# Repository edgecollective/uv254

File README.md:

# uv254

**[⬇ Download the latest files (zip)](https://github.com/edgecollective/uv254/archive/refs/heads/main.zip)**:
everything on `main` (all three KiCad boards, the shared parts library and the
firmware), as of the [latest commit](https://github.com/edgecollective/uv254/commit/main).
Unzip it and keep the folders together.

**Release v0.6** (2026-11-23), the three boards as one set that work together:
gerbers for the [detector](https://github.com/edgecollective/uv254/releases/download/uv-detector/v0.6/uv-detector-v0.6-gerbers.zip),
[emitter](https://github.com/edgecollective/uv254/releases/download/uv-emitter/v0.6/uv-emitter-v0.6-gerbers.zip) and
[control](https://github.com/edgecollective/uv254/releases/download/uv-control/v0.6/uv-control-v0.6-gerbers.zip) boards
(release pages: [detector](https://github.com/edgecollective/uv254/releases/tag/uv-detector/v0.6),
[emitter](https://github.com/edgecollective/uv254/releases/tag/uv-emitter/v0.6),
[control](https://github.com/edgecollective/uv254/releases/tag/uv-control/v0.6)), or
**[⬇ the whole design at this release (zip)](https://github.com/edgecollective/uv254/archive/refs/tags/uv-control/v0.6.zip)**.
Unlike the "latest" link above, these stay the same when more commits are pushed.

Open hardware for the **uv254** UV water-quality sensor. The device is three
boards, each its own KiCad project:

| Board | Folder | What's on it | Current design |
|---|---|---|---|
| **UV-Control** | [`hardware/uv-control`](hardware/uv-control) | Adafruit Feather controller (nRF52840 or ESP32-S3), ADS1115 ADC, color TFT, microSD, buttons, 12 V LED boost | v0.6 (released 2026-11-23) |
| **UV-Emitter** | [`hardware/uv-emitter`](hardware/uv-emitter) | Inolux IN-C35PPCTGU0 UV-C LED and its driver | v0.6 (released 2026-11-23: 3.3 V, 12 V LED supply, MMBT3904 driver) |
| **UV-Detector** | [`hardware/uv-detector`](hardware/uv-detector) | SD008-2171-112 photodiode with an op-amp front end | v0.6 (released 2026-11-23: 3.3 V, 1.8 V reference, 7-pin connector) |

| [UV-Control](hardware/uv-control) | [UV-Emitter](hardware/uv-emitter) | [UV-Detector](hardware/uv-detector) |
|:---:|:---:|:---:|
|  |  |  |

Each board's README has its schematic, PCB layout and 3D views.

**Open work:** [`hardware/uv-control/TODO.md`](hardware/uv-control/TODO.md) is
the to-do list for the control board (v0.4 layout in progress). If you're a
person or an agent picking up the work, read it and
[CONTRIBUTING.md](CONTRIBUTING.md) first.

**Bill of materials:** [`hardware/BOM.md`](hardware/BOM.md) lists the parts for
one set of boards and the cables between them, with manufacturer part numbers.
The same list is on the [project web page](https://edgecollective.io/uv254/bom/),
which scales it to several sets and downloads it as a CSV for Digi-Key's or
Mouser's BOM upload.

UV-Emitter was called *UV-LED-source* in earlier revisions. Background notes
are at <https://edgecollective.io/notes/uvf/>.

## Repository layout

```
hardware/
  BOM.md, bom.csv             parts for one set of boards and cables, with part numbers
  uv-control/                 one KiCad project per board
    uv-control.kicad_pro      open this in KiCad
    uv-control.kicad_sch
    uv-control.kicad_pcb
    TODO.md                   open work on that board (uv-control has one)
    sym-lib-table             -> lib/uv254.kicad_sym
    fp-lib-table              -> lib/uv254.pretty
    docs/                     schematic PDF and the images in the board's README
    fab/<version>/            fabrication files that were actually sent out
  uv-emitter/
  uv-detector/
lib/                          shared project library (custom parts only)
  uv254.kicad_sym
  uv254.pretty/
firmware/uv-control/          CircuitPython scripts for the control board
docs/                         project web page (GitHub Pages): edgecollective.io/uv254
  bom/index.html              the bill of materials page, made by scripts/make-bom.py
scripts/build-fab.sh          builds gerbers, drill, BOM, PDF, positions
scripts/render-images.sh      renders schematic, layout and 3D images for the READMEs
scripts/make-bom.py           builds BOM.md, bom.csv and the BOM web page from the schematics
.github/workflows/kicad.yml   ERC/DRC on every push; fab package on release tags
```

## Opening the boards

**[Download the latest design files (zip)](https://github.com/edgecollective/uv254/archive/refs/heads/main.zip)** if you just want to look
at or build the boards, or clone the repository to work on them. Either way,
open `hardware/<board>/<board>.kicad_pro` in **KiCad 10.0.x**, the version
everyone on the project uses (see [CONTRIBUTING.md](CONTRIBUTING.md)).

Keep the folder structure as it is. Custom parts come from `lib/` through each
project's own library tables, so you don't need any global library setup beyond
KiCad's standard libraries, but a board folder copied out on its own will be
missing its custom parts.

## Updating the board images

Each board's README shows its schematic, PCB layout and 3D views. These are
files in `hardware/<board>/docs/`, made by `scripts/render-images.sh`, so they
don't change by themselves when the design does. After changing a board, save
it in KiCad, then refresh the images from the top of the repository:

```sh
scripts/render-images.sh uv-detector                         # one board
scripts/render-images.sh uv-control uv-detector uv-emitter   # all three
```

Then commit what changed (`git status` shows it) along with the design change.

What the script does:

- Writes to `hardware/<board>/docs/`: the schematic as PDF and PNG, the PCB
  layout front and back (the back mirrored, as seen from below), and 3D renders
  front and back.
- Updates the image section of the board's README, between the
  `render-images` markers. Anything you write between those markers gets
  overwritten, so put your own notes outside them.
- Only replaces files whose picture changed. A board whose 3D look changed
  takes about 2 minutes (two raytraced renders). An unchanged board takes about
  15 seconds and leaves git clean.
- Uses KiCad's default colour theme, so everyone's images come out the same
  whatever their own KiCad preferences.

For a quick look while you work, `--fast` makes flat-shaded 3D renders in a few
seconds. Commit the full renders, though: run it again without `--fast` before
committing.

It needs KiCad 10 (`kicad-cli` on your `PATH`), plus Inkscape, ImageMagick and
poppler. On Debian or Ubuntu:

```sh
sudo apt install inkscape imagemagick poppler-utils
```

It has only been tested on Linux.

## Updating the bill of materials

`hardware/BOM.md`, `hardware/bom.csv` and the web page `docs/bom/index.html`
are made by `scripts/make-bom.py` from the three schematics. After adding,
removing or changing parts, run it from the top of the repository and commit
what changed:

```sh
scripts/make-bom.py
```

The schematics don't carry part numbers, so the script keeps its own table of
them (`PARTS`, near the top). If a schematic has a part the script doesn't
know, it stops and names it: add a line for it to `PARTS` and to `part_for()`.
Files only change when the parts do, so re-running leaves git clean otherwise.
It needs `kicad-cli` on your `PATH`.

The web page is served by GitHub Pages from the `docs/` folder on `main`, at
<https://edgecollective.io/uv254/>, the address printed on the detector and
emitter boards. It updates a minute or so after a push.

## Versions and releases

Each board is versioned on its own. A revision is a git tag named
`<board>/<version>`:

```
git tag -l 'uv-detector/*'          # list detector revisions
git checkout uv-detector/v0.3       # the exact design ordered from JLCPCB in Aug 2024
git checkout main                   # back to the current work
```

To download one revision as a zip, use its tag, for example
<https://github.com/edgecollective/uv254/archive/refs/tags/uv-detector/v0.3.zip>.

`hardware/<board>/fab/<version>/` holds the files that were actually sent to
the fab house for that revision. Each board's README has the revision history.
Pushing a new tag makes CI build that board's fab package and attach it to a
GitHub Release (see [CONTRIBUTING.md](CONTRIBUTING.md#releasing-a-board-revision)).

The history before this repository is in
[gitlab.com/edgecollective/uv-water](https://gitlab.com/edgecollective/uv-water).
Every tagged revision here was imported from it. The imported fab files were
checked by regenerating them from the tagged design.

## License

- **Hardware** (everything except `firmware/`): [CERN Open Hardware Licence
  Version 2 – Strongly Reciprocal](LICENSE) (CERN-OHL-S-2.0).
- **Exception:** `lib/uv254.3dshapes/Adafruit_Feather_nRF52840_4062.step` and
  `Adafruit_TPS61040_Boost_5644.step` are Adafruit's 3D models, under the MIT
  License ([notice](lib/uv254.3dshapes/Adafruit_CAD_Parts-LICENSE.txt)).
- **Firmware** (`firmware/`): [MIT License](firmware/uv-control/LICENSE). The
  bundled Adafruit libraries are also MIT, under Adafruit's copyright.

Contributors: Don Blair, Craig Versek.

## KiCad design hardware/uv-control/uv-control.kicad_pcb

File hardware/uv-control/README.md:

# UV-Control

Controller board. **v0.6 was released on 2026-11-23** (tag `uv-control/v0.6`,
fab files in [`fab/v0.6`](fab/v0.6)), with the detector and emitter v0.6 it connects to. It was restarted from Rook v0.4 (Edge
Collective's validated Pro Micro nRF52840 board) and keeps its ST7789 display,
buttons and microSD, with an **Adafruit Feather** (nRF52840 or ESP32-S3, M4 as
fallback) as the controller, an ADS1115 ADC, JST connectors to the emitter and
detector, test headers, a power switch, and a TPS61041 boost that makes the UV
LED's 12 V (or Adafruit's 5644 boost breakout at J8). Firmware is moving to Arduino.
See [`v0.4-design.md`](v0.4-design.md) for the pin map. The
first v0.4 draft is in [`reference/v0.4-draft`](reference/v0.4-draft).

**Open work: [`TODO.md`](TODO.md)** lists what's left before ordering, with
part references, coordinates and how to check each item. Start there if you're
picking up this board (people and agents alike).

v0.1 (fabricated in 2024) used an Adafruit ItsyBitsy nRF52840 Express, an
SSD1306 OLED display, push buttons and a 555-based boost circuit.

Firmware is in [`firmware/uv-control`](../../firmware/uv-control). The v0.4
bring-up code is in its [`v0.4`](../../firmware/uv-control/v0.4) folder.

Open `uv-control.kicad_pro` in KiCad 10. Custom parts come from
[`lib/`](../../lib).

**[Download the KiCad files (zip)](https://github.com/edgecollective/uv254/archive/refs/heads/main.zip)**: the whole repository as it is on
`main`, because the board needs the shared `lib/` folder. This board is in
`hardware/uv-control/`.

<!-- render-images:start -->
<!-- Generated by scripts/render-images.sh. Edits between these markers are overwritten. -->

## Schematic

Click the image for the [PDF](docs/uv-control-schematic.pdf).

## Board layout

Copper and silkscreen. The back is mirrored, as seen from below.

| Front | Back |
|:---:|:---:|
|  |  |

## 3D view

| Front | Back |
|:---:|:---:|
|  |  |

Images of the current design, made with `scripts/render-images.sh uv-control`.
Re-run it after changing the board; see
[Updating the board images](../../README.md#updating-the-board-images).
<!-- render-images:end -->

## Revisions

| Version | Date | Status | Design | Fab files |
|---|---|---|---|---|
| v0.1 | 2024-07-29 | gerbers released; ordered from JLCPCB on 2024-08-19 | tag `uv-control/v0.1` | [`fab/v0.1`](fab/v0.1) |
| v0.1_A | 2026-06-26 | branched from v0.1; sent to Josh | tag `uv-control/v0.1_A` | — |
| v0.1_A+ | 2026-10 | edits made after v0.1_A was sent; never fabricated; superseded by v0.4 | commit `db4232b` | — |
| v0.4 | 2026-11-23 | tagged, then renumbered v0.5 before ordering (same design) | tag `uv-control/v0.4` | [`fab/v0.4`](fab/v0.4) |
| v0.5 | 2026-11-23 | released, then superseded by v0.6 before ordering | tag `uv-control/v0.5` | [`fab/v0.5`](fab/v0.5) |
| **v0.6** | 2026-11-23 | **released**: v0.5 plus pin labels at the display header; for detector and emitter v0.6 (open items in [`TODO.md`](TODO.md)) | tag `uv-control/v0.6` | [`fab/v0.6`](fab/v0.6) |

Notes:

- **v0.1_A+** isn't tagged. To get it back: `git checkout db4232b -- hardware/uv-control`.
  Its silkscreen points to `gitlab.com/edgecollective/uv-water/` and reads
  `UV-Control v0.1 / July 2024`.

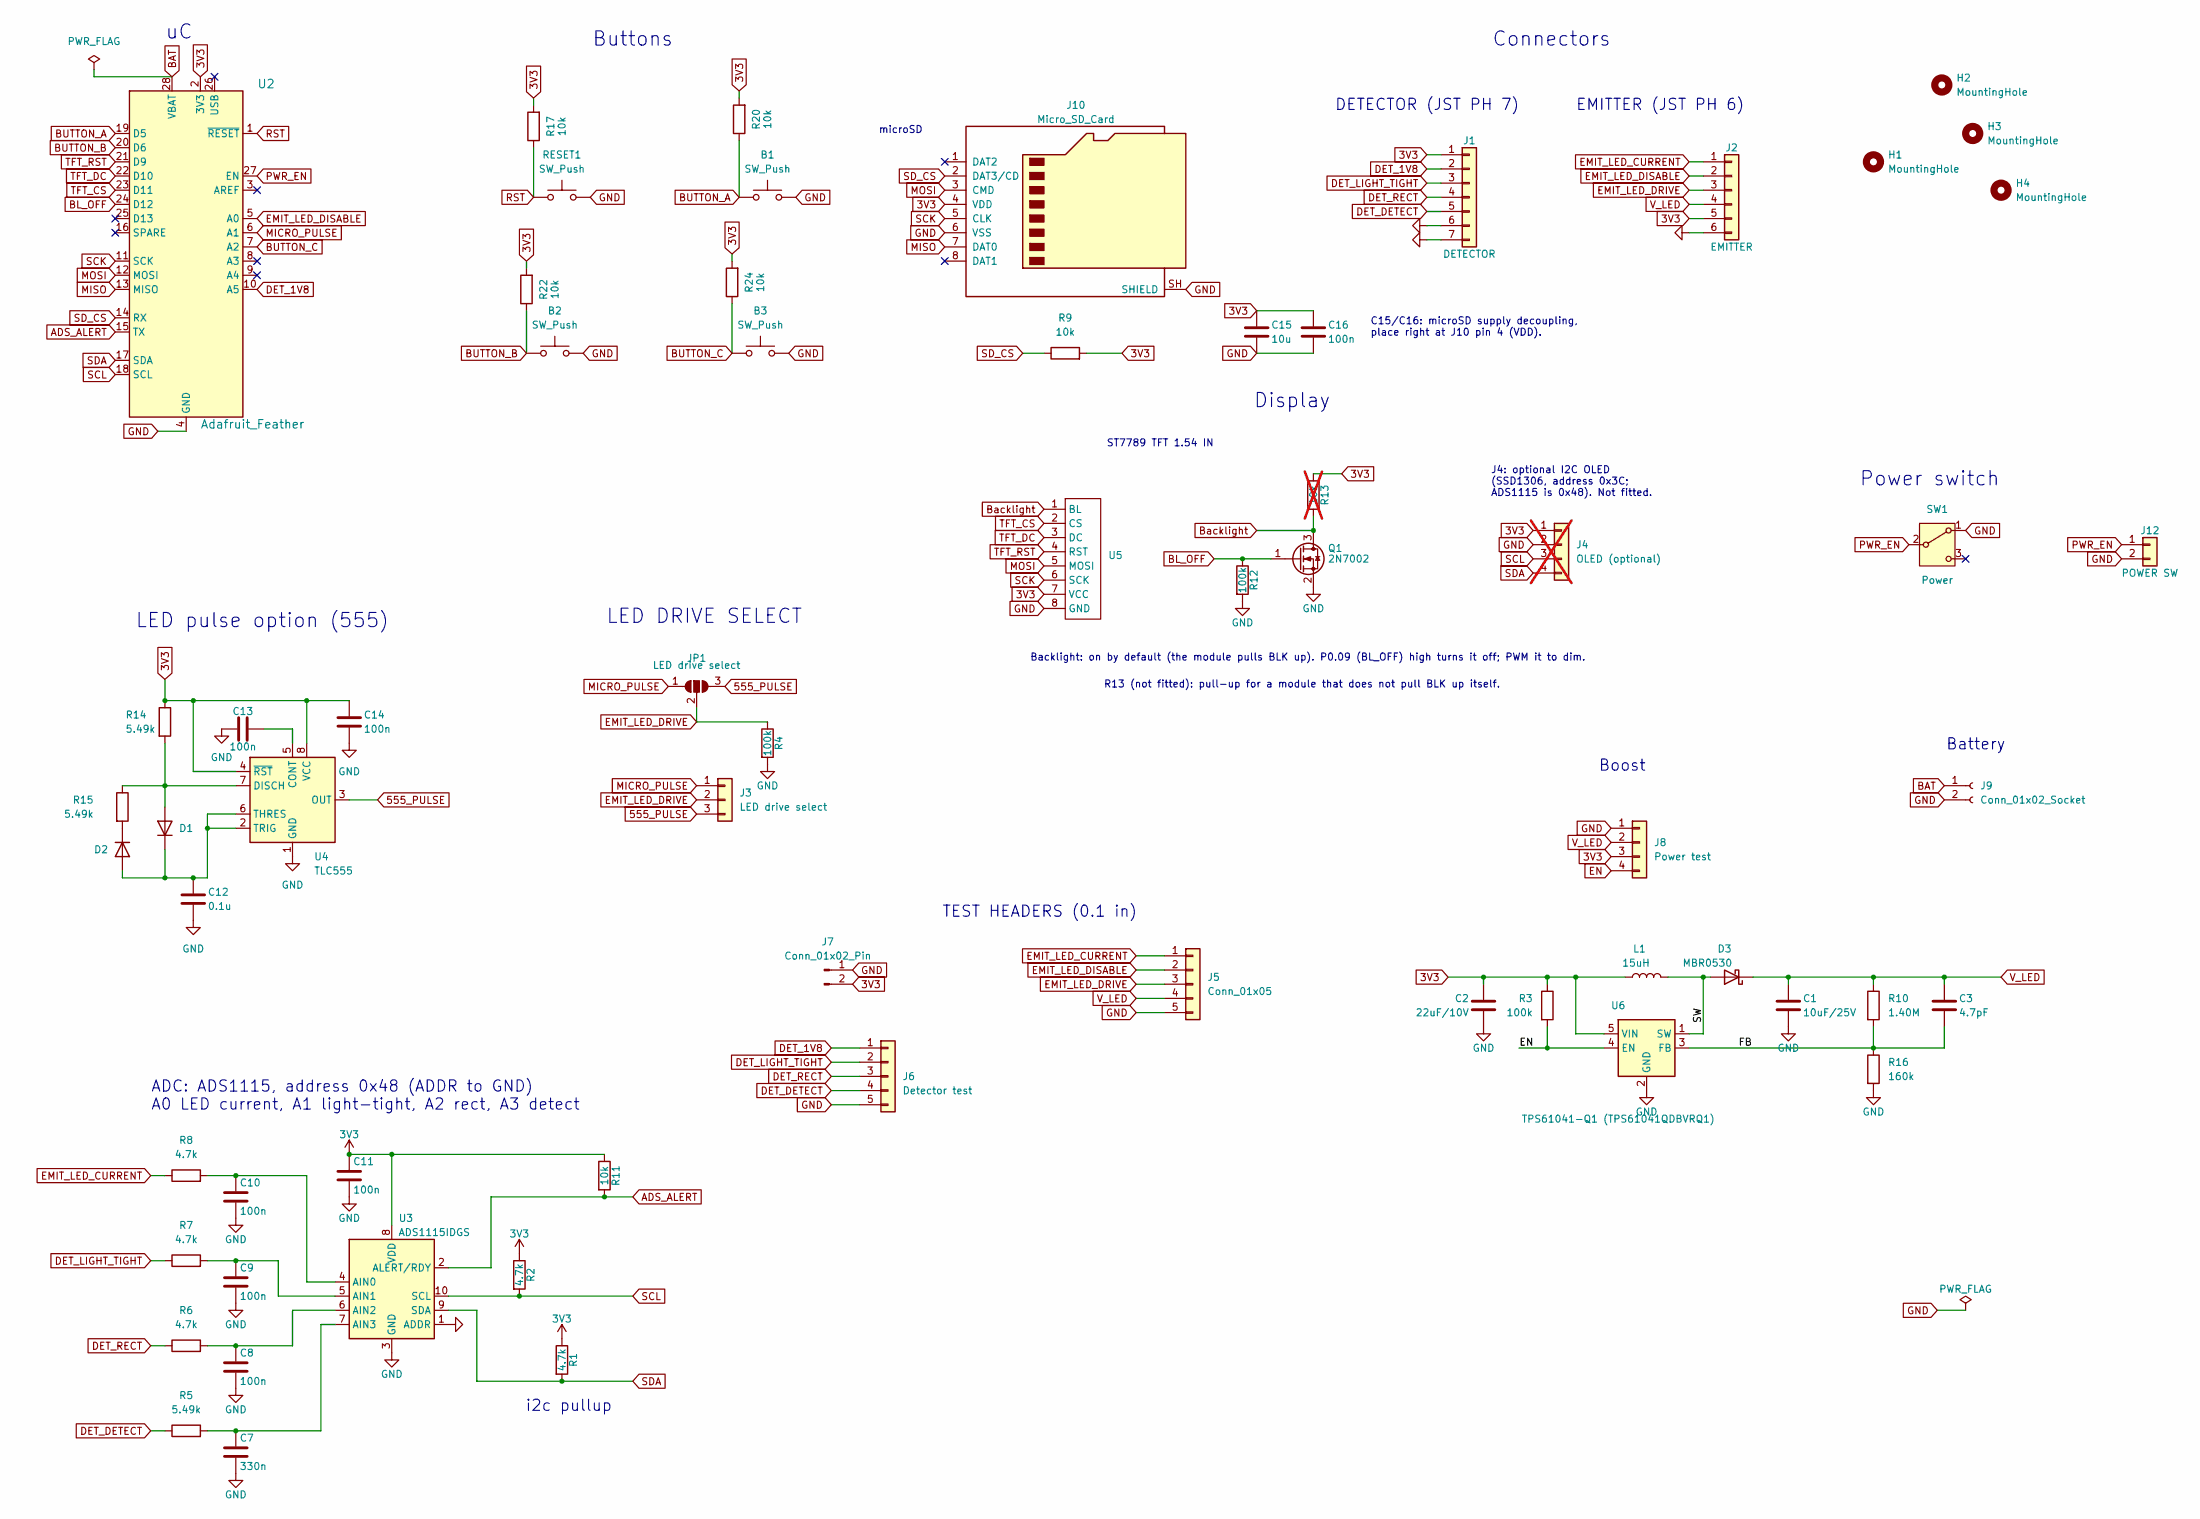
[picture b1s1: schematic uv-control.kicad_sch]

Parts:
B1, B2, B3: SW_Push; SW_Tactile_12x12_B3F-40xx
C1: 10uF/25V; C_0805_2012Metric
C2: 22uF/10V; C_0805_2012Metric
C3: 4.7pF; C_0805_2012Metric
C7: 330n; C_0805_2012Metric
C8, C9, C10, C11, C13, C14, C16: 100n; C_0805_2012Metric
C12: 0.1u; C_0805_2012Metric
C15: 10u; C_0805_2012Metric
D1, D2: 1N4148W; D_SOD-123
D3: MBR0530; D_SOD-123
H1, H2, H3, H4: MountingHole; MountingHole_3.2mm_M3
J1: DETECTOR; JST_PH_B7B-PH-K_1x07_P2.00mm_Vertical
J2: EMITTER; JST_PH_B6B-PH-K_1x06_P2.00mm_Vertical
J3: LED drive select; PinHeader_1x03_P2.54mm_Vertical
J4: OLED (optional); ssd1306_a; not fitted
J5: Conn_01x05; PinHeader_1x05_P2.54mm_Vertical
J6: Detector test; PinHeader_1x05_P2.54mm_Vertical
J7: Conn_01x02_Pin; PinHeader_1x02_P2.54mm_Vertical
J8: Power test; Adafruit_TPS61040_Boost_5644
J9: Conn_01x02_Socket; JST_PH_B2B-PH-K_1x02_P2.00mm_Vertical
J10: Micro_SD_Card; DM3D-SF_outline
J12: POWER SW; PinHeader_1x02_P2.54mm_Vertical
JP1: LED drive select; SolderJumper-3_P1.3mm_Open_RoundedPad1.0x1.5mm_NumberLabels
L1: 15uH; L_1210_3225Metric
Q1: 2N7002; SOT-23
R1, R2, R6, R7, R8: 4.7k; R_0805_2012Metric
R3: 100k; R_0603_1608Metric
R4, R12: 100k; R_0805_2012Metric
R5, R14, R15: 5.49k; R_0805_2012Metric
R9, R17, R20, R22, R24: 10k; R_0805_2012Metric_Pad1.20x1.40mm_HandSolder
R10: 1.40M; R_0805_2012Metric_Pad1.20x1.40mm_HandSolder
R11: 10k; R_0805_2012Metric
R13: 10k; R_0805_2012Metric; not fitted
R16: 160k; R_0805_2012Metric
RESET1: SW_Push; SW_PUSH_6mm_H5mm
SW1: Power; SW_Slide_SPDT_Angled_CK_OS102011MA1Q
U2: Adafruit_Feather; Adafruit_Feather_on_socket_WithMountingHoles
U3: ADS1115IDGS; TSSOP-10_3x3mm_P0.5mm
U4: TLC555; SOIC-8_3.9x4.9mm_P1.27mm
U5: st7789_200in_240x320
U6: TPS61041-Q1 (TPS61041QDBVRQ1); SOT-23-5

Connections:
3V3: C2.1, C11.1, C14.1, C15.1, C16.1, J1.1, J2.5, J4.1, J7.2, J8.3, J10.4 (VDD), L1.1, R1.1, R2.1, R3.1, R9.2, R11.1, R13.1, R14.1, R17.2, R20.2, R22.2, R24.2, U2.2 (3V3), U3.8 (VDD), U4.4 (~RST), U4.8 (VCC), U5.7 (VCC), U6.5 (VIN)
555_PULSE: J3.3, JP1.3 (B), U4.3 (OUT)
/FB: C3.2, R10.2, R16.1, U6.3 (FB)
/SW: D3.2 (A), L1.2, U6.1 (SW)
ADS_ALERT: R11.2, U2.15 (TX), U3.2 (ALERT/RDY)
BAT: J9.1, U2.28 (VBAT)
BL_OFF: Q1.1 (G), R12.1, U2.24 (D12)
BUTTON_A: B1.1, R20.1, U2.19 (D5)
BUTTON_B: B2.1, R22.1, U2.20 (D6)
BUTTON_C: B3.1, R24.1, U2.7 (A2)
Backlight: Q1.3 (D), R13.2, U5.1 (BL)
DET_1V8: J1.2, J6.1, U2.10 (A5)
DET_DETECT: J1.5, J6.4, R5.1
DET_LIGHT_TIGHT: J1.3, J6.2, R7.1
DET_RECT: J1.4, J6.3, R6.1
EMIT_LED_CURRENT: J2.1, J5.1, R8.1
EMIT_LED_DISABLE: J2.2, J5.2, U2.5 (A0)
EMIT_LED_DRIVE: J2.3, J3.2, J5.3, JP1.2 (C), R4.1
EN: J8.4, R3.2, U6.4 (EN)
GND: B1.2, B2.2, B3.2, C1.2, C2.2, C7.2, C8.2, C9.2, C10.2, C11.2, C12.2, C13.1, C14.2, C15.2, C16.2, J1.6, J1.7, J2.6, J4.2, J5.5, J6.5, J7.1, J8.1, J9.2, J10.6 (VSS), J10.SH (SHIELD), J12.2, Q1.2 (S), R4.2, R12.2, R16.2, RESET1.2, SW1.1 (A), U2.4 (GND), U3.1 (ADDR), U3.3 (GND), U4.1 (GND), U5.8 (GND), U6.2 (GND)
MICRO_PULSE: J3.1, JP1.1 (A), U2.6 (A1)
MISO: J10.7 (DAT0), U2.13 (MISO)
MOSI: J10.3 (CMD), U2.12 (MOSI), U5.5 (MOSI)
unnamed: D1.2 (A), R14.2, R15.1, U4.7 (DISCH)
unnamed: C12.1, D1.1 (K), D2.2 (A), U4.2 (TRIG), U4.6 (THRES)
unnamed: D2.1 (K), R15.2
unnamed: C10.1, R8.2, U3.4 (AIN0)
unnamed: C9.1, R7.2, U3.5 (AIN1)
unnamed: C8.1, R6.2, U3.6 (AIN2)
unnamed: C7.1, R5.2, U3.7 (AIN3)
unnamed: C13.2, U4.5 (CONT)
PWR_EN: J12.1, SW1.2 (B), U2.27 (EN)
RST: R17.1, RESET1.1, U2.1 (~RESET)
SCK: J10.5 (CLK), U2.11 (SCK), U5.6 (SCK)
SCL: J4.3, R2.2, U2.18 (SCL), U3.10 (SCL)
SDA: J4.4, R1.2, U2.17 (SDA), U3.9 (SDA)
SD_CS: J10.2 (DAT3/CD), R9.1, U2.14 (RX)
TFT_CS: U2.23 (D11), U5.2 (CS)
TFT_DC: U2.22 (D10), U5.3 (DC)
TFT_RST: U2.21 (D9), U5.4 (RST)
V_LED: C1.1, C3.1, D3.1 (K), J2.4, J5.4, J8.2, R10.1

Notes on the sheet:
LED DRIVE SELECT
Boost
microSD
EMITTER (JST PH 6)
Display
TEST HEADERS (0.1 in)
ADC: ADS1115, address 0x48 (ADDR to GND) A0 LED current, A1 light-tight, A2 rect, A3 detect
ST7789 TFT 1.54 IN
Connectors
Battery
i2c pullup
DETECTOR (JST PH 7)
Power switch
Backlight: on by default (the module pulls BLK up). P0.09 (BL_OFF) high turns it off; PWM it to dim.
C15/C16: microSD supply decoupling, place right at J10 pin 4 (VDD).
Buttons
LED pulse option (555)
R13 (not fitted): pull-up for a module that does not pull BLK up itself.
J4: optional I2C OLED (SSD1306, address 0x3C; ADS1115 is 0x48). Not fitted.

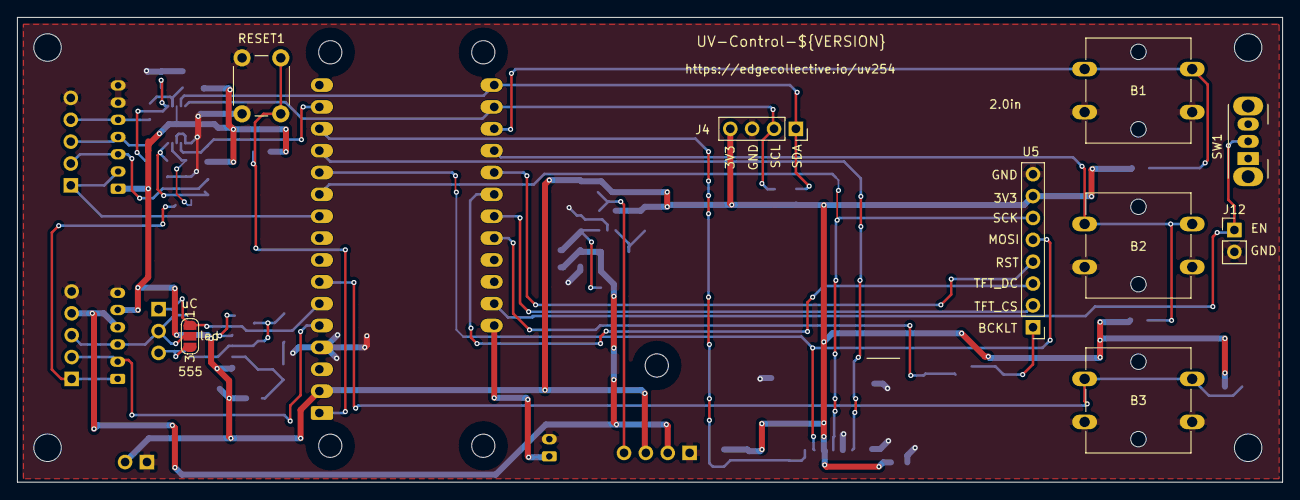
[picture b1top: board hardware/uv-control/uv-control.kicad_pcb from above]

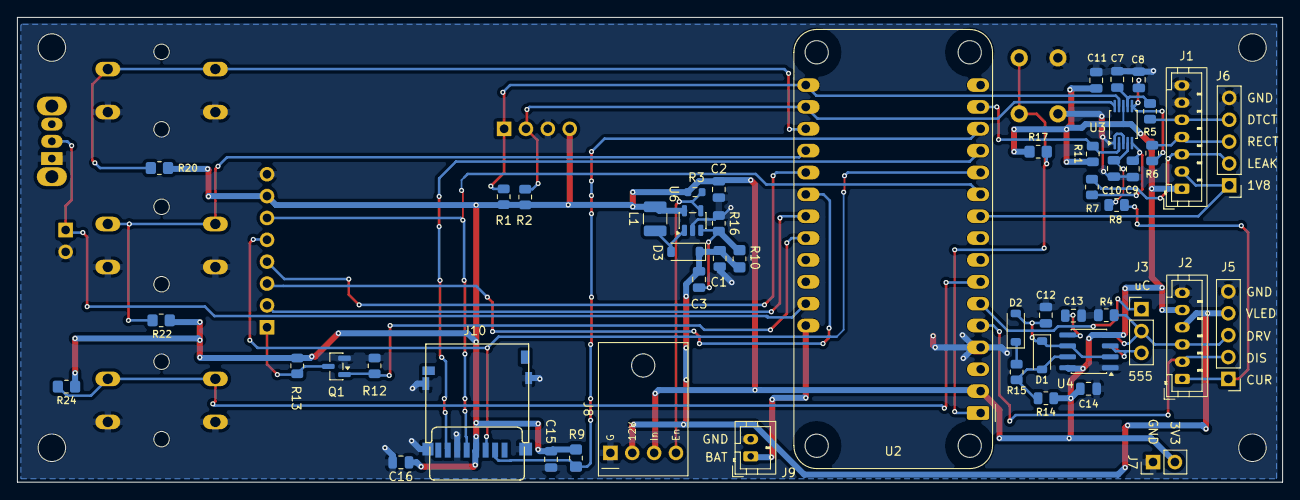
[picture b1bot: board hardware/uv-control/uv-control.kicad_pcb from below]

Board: 2 copper layers, 147.0 x 54.0 mm, 64 parts (51 on the bottom side), 41 nets.

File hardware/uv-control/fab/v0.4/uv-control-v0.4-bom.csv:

"Refs","Value","Footprint","Qty","DNP","Description"
"B1,B2,B3","SW_Push","uv254:SW_Tactile_12x12_B3F-40xx","3","","Push button switch, generic, two pins"
"C1","10uF/25V","Capacitor_SMD:C_0805_2012Metric","1","",""
"C2","22uF/10V","Capacitor_SMD:C_0805_2012Metric","1","",""
"C3","4.7pF","Capacitor_SMD:C_0805_2012Metric","1","",""
"C7","330n","Capacitor_SMD:C_0805_2012Metric","1","","Unpolarized capacitor"
"C8,C9,C10,C11,C13,C14,C16","100n","Capacitor_SMD:C_0805_2012Metric","7","","Unpolarized capacitor"
"C12","0.1u","Capacitor_SMD:C_0805_2012Metric","1","","Unpolarized capacitor"
"C15","10u","Capacitor_SMD:C_0805_2012Metric","1","","Unpolarized capacitor"
"D1,D2","1N4148W","Diode_SMD:D_SOD-123","2","","75V 0.15A Fast Switching Diode, SOD-123"
"D3","MBR0530","Diode_SMD:D_SOD-123","1","",""
"J1","DETECTOR","Connector_JST:JST_PH_B7B-PH-K_1x07_P2.00mm_Vertical","1","","Generic connector, single row, 01x07, script generated (kicad-library-utils/schlib/autogen/connector/)"
"J2","EMITTER","Connector_JST:JST_PH_B6B-PH-K_1x06_P2.00mm_Vertical","1","","Generic connector, single row, 01x06, script generated (kicad-library-utils/schlib/autogen/connector/)"
"J3","LED drive select","Connector_PinHeader_2.54mm:PinHeader_1x03_P2.54mm_Vertical","1","","Generic connector, single row, 01x03, script generated (kicad-library-utils/schlib/autogen/connector/)"
"J4","OLED (optional)","uv254:ssd1306_a","1","DNP","Generic connector, single row, 01x04, script generated (kicad-library-utils/schlib/autogen/connector/)"
"J5","Conn_01x05","Connector_PinHeader_2.54mm:PinHeader_1x05_P2.54mm_Vertical","1","","Generic connector, single row, 01x05, script generated (kicad-library-utils/schlib/autogen/connector/)"
"J6","Detector test","Connector_PinHeader_2.54mm:PinHeader_1x05_P2.54mm_Vertical","1","","Generic connector, single row, 01x05, script generated (kicad-library-utils/schlib/autogen/connector/)"
"J7","Conn_01x02_Pin","Connector_PinHeader_2.54mm:PinHeader_1x02_P2.54mm_Vertical","1","","Generic connector, single row, 01x02, script generated"
"J8","Power test","uv254:Adafruit_TPS61040_Boost_5644","1","","Generic connector, single row, 01x04, script generated (kicad-library-utils/schlib/autogen/connector/)"
"J9","Conn_01x02_Socket","Connector_JST:JST_PH_B2B-PH-K_1x02_P2.00mm_Vertical","1","","Generic connector, single row, 01x02, script generated"
"J10","Micro_SD_Card","uv254:DM3D-SF_outline","1","","Micro SD Card Socket"
"J12","POWER SW","Connector_PinHeader_2.54mm:PinHeader_1x02_P2.54mm_Vertical","1","","Panel-mount power switch (e.g. a rocker), in parallel with SW1: closed pulls the Feather EN pin to GND (off)"
"L1","15uH","Inductor_SMD:L_1210_3225Metric","1","",""
"Q1","2N7002","Package_TO_SOT_SMD:SOT-23","1","","0.115A Id, 60V Vds, N-Channel MOSFET, SOT-23"
"R1,R2,R6,R7,R8","4.7k","Resistor_SMD:R_0805_2012Metric","5","","Resistor"
"R3","100k","Resistor_SMD:R_0603_1608Metric","1","",""
"R4,R12","100k","Resistor_SMD:R_0805_2012Metric","2","","Resistor"
"R5,R14,R15","5.49k","Resistor_SMD:R_0805_2012Metric","3","","Resistor"
"R9,R17,R20,R22,R24","10k","Resistor_SMD:R_0805_2012Metric_Pad1.20x1.40mm_HandSolder","5","","Resistor"
"R10","1.40M","Resistor_SMD:R_0805_2012Metric_Pad1.20x1.40mm_HandSolder","1","",""
"R11,R13","10k","Resistor_SMD:R_0805_2012Metric","2","DNP","Resistor"
"R16","160k","Resistor_SMD:R_0805_2012Metric","1","",""
"RESET1","SW_Push","Button_Switch_THT:SW_PUSH_6mm_H5mm","1","","Push button switch, generic, two pins"
"SW1","Power","Button_Switch_THT:SW_Slide_SPDT_Angled_CK_OS102011MA1Q","1","","Power switch: B-A pulls the Feather EN pin to GND (off)"
"U2","Adafruit_Feather","uv254:Adafruit_Feather_on_socket_WithMountingHoles","1","","Adafruit Feather (any board with the standard Feather pinout). Pins are named by their silkscreen labels; on the nRF52840, ESP32-S3 and M4 Feathers these are also the Arduino pin numbers. 3V3 is the Feather's regulator output."
"U3","ADS1115IDGS","Package_SO:TSSOP-10_3x3mm_P0.5mm","1","","Ultra-Small, Low-Power, I2C-Compatible, 860-SPS, 16-Bit ADCs With Internal Reference, Oscillator, and Programmable Comparator, VSSOP-10"
"U4","TLC555","Package_SO:SOIC-8_3.9x4.9mm_P1.27mm","1","","Single LinCMOS Timer, 555 compatible, SOIC-8"
"U5","","uv254:st7789_200in_240x320","1","",""
"U6","TPS61041-Q1 (TPS61041QDBVRQ1)","Package_TO_SOT_SMD:SOT-23-5","1","",""

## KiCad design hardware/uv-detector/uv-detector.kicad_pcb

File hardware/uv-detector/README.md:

# UV-Detector

Photodiode board: an SD008-2171-112 photodiode with an OPA4340 op-amp front
end. From v0.5 it runs from 3.3 V, with an MCP1501-18 1.8 V reference.

The cable connector is a 7-pin JST PH (J2), with a 0.1" header (J1) in
parallel:

| Pin | 1 | 2 | 3 | 4 | 5 | 6 | 7 |
|---|---|---|---|---|---|---|---|
| Signal | 3V3 | 1V8 (reference out) | light-tight (`LEAK`) | rect (`RECT`) | detect (`DTCT`) | GND | GND |

Open `uv-detector.kicad_pro` in KiCad 10. Custom parts come from
[`lib/`](../../lib).

**[Download the KiCad files (zip)](https://github.com/edgecollective/uv254/archive/refs/heads/main.zip)**: the whole repository as it is on
`main`, because the board needs the shared `lib/` folder. This board is in
`hardware/uv-detector/`.

<!-- render-images:start -->
<!-- Generated by scripts/render-images.sh. Edits between these markers are overwritten. -->

## Schematic

Click the image for the [PDF](docs/uv-detector-schematic.pdf).

## Board layout

Copper and silkscreen. The back is mirrored, as seen from below.

| Front | Back |
|:---:|:---:|
|  |  |

## 3D view

| Front | Back |
|:---:|:---:|
|  |  |

Images of the current design, made with `scripts/render-images.sh uv-detector`.
Re-run it after changing the board; see
[Updating the board images](../../README.md#updating-the-board-images).
<!-- render-images:end -->

## Revisions

| Version | Date | Status | Design | Fab files |
|---|---|---|---|---|
| v0.1 | 2024-03-12 | gerbers released | tag `uv-detector/v0.1` | [`fab/v0.1`](fab/v0.1) |
| v0.2 | 2024-04-06 | gerbers released | tag `uv-detector/v0.2` | [`fab/v0.2`](fab/v0.2) |
| v0.3 | 2024-08-19 | ordered from JLCPCB with emitter v0.3 and control v0.1 | tag `uv-detector/v0.3` | [`fab/v0.3`](fab/v0.3) |
| v0.2_A | 2026-06-26 | branched from v0.2; sent to Josh | tag `uv-detector/v0.2_A` | — |
| v0.2_B | 2026-10 | follows v0.2_A | tag `uv-detector/v0.2_B` | — |
| v0.4 | 2026-11-08 | gerbers released; derived from v0.2_B (5 V, 6-pin connector) | tag `uv-detector/v0.4` | [`fab/v0.4`](fab/v0.4) |
| v0.5 | 2026-11-23 | gerbers released, then renumbered v0.6 with the set before ordering (same design) | tag `uv-detector/v0.5` | [`fab/v0.5`](fab/v0.5) |
| **v0.6** | 2026-11-23 | **gerbers released**: 3.3 V, 1.8 V reference, 7-pin connector; for UV-Control v0.6 | tag `uv-detector/v0.6` | [`fab/v0.6`](fab/v0.6) |

Notes:

- **v0.2**: the fabricated gerbers also include the copper text
  `uva-detect-v0.2` on F.Cu. It was deleted from the board before the design
  was committed. See [`fab/v0.2/README.md`](fab/v0.2/README.md).
- **v0.3** has no `.kicad_pro`, because it was never committed upstream. Open
  `uv-detector.kicad_pcb` or `.kicad_sch` directly at that tag.
- **v0.4** was called "v0.3" in `uv-water`. It was renumbered because v0.3 was
  already used by the 2024 JLCPCB order.
- **v0.5** (in progress) moves to the system-wide 3.3 V supply: the op-amp runs
  from 3.3 V instead of 5 V, and an MCP1501-18 (1.8 V, buffered) replaces the
  LM4040 2.5 V shunt reference and its feed resistor. The connectors grow from
  6 to 7 pins, the extra pin being a second GND. Signal swing above the
  reference drops from 2.5 V to 1.5 V, so the gain values may need adjusting.

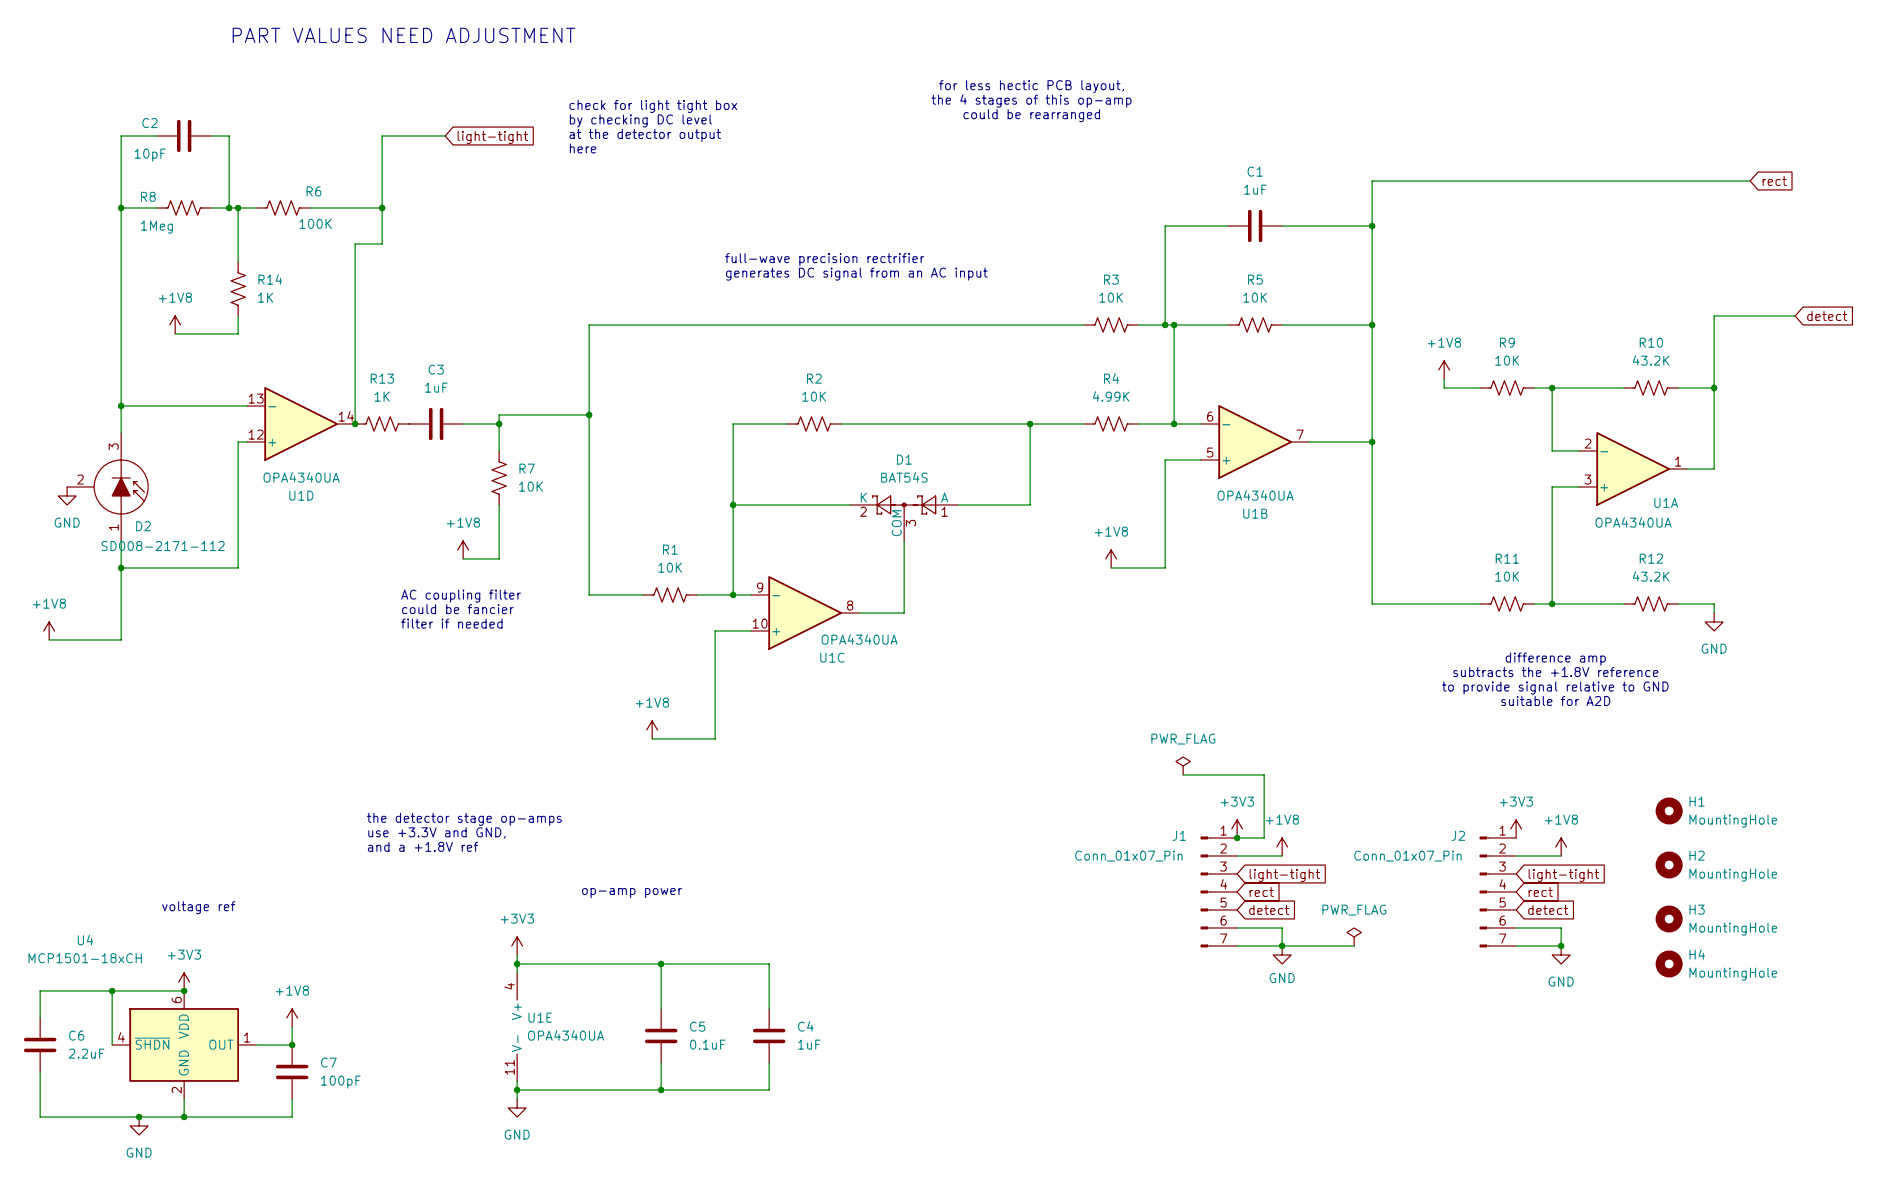
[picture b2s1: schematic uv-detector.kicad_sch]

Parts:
C1, C3, C4: 1uF; C_0805_2012Metric_Pad1.18x1.45mm_HandSolder
C2: 10pF; C_0805_2012Metric_Pad1.18x1.45mm_HandSolder
C5: 0.1uF; C_0805_2012Metric_Pad1.18x1.45mm_HandSolder
C6: 2.2uF; C_0805_2012Metric_Pad1.18x1.45mm_HandSolder
C7: 100pF; C_0805_2012Metric_Pad1.18x1.45mm_HandSolder
D1: BAT54S; SOT-23
D2: SD008-2171-112; TO-18-3
H1, H2, H3, H4: MountingHole; MountingHole_3.2mm_M3
J1: Conn_01x07_Pin; PinHeader_1x07_P2.54mm_Vertical
J2: Conn_01x07_Pin; JST_PH_B7B-PH-K_1x07_P2.00mm_Vertical
R1, R2, R3, R5, R7, R9, R11: 10K; R_0805_2012Metric_Pad1.20x1.40mm_HandSolder
R4: 4.99K; R_0805_2012Metric_Pad1.20x1.40mm_HandSolder
R6: 100K; R_0805_2012Metric_Pad1.20x1.40mm_HandSolder
R8: 1Meg; R_0805_2012Metric_Pad1.20x1.40mm_HandSolder
R10, R12: 43.2K; R_0805_2012Metric_Pad1.20x1.40mm_HandSolder
R13, R14: 1K; R_0805_2012Metric_Pad1.20x1.40mm_HandSolder
U1: OPA4340UA; SOIC-14_3.9x8.7mm_P1.27mm
U4: MCP1501-18xCH; SOT-23-6

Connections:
+1V8: C7.2, D2.1, J1.2, J2.2, R7.1, R9.1, R14.1, U1.5 (+), U1.10 (+), U1.12 (+), U4.1 (OUT)
+3V3: C4.2, C5.2, C6.2, J1.1, J2.1, U1.4 (V+), U4.4 (~SHDN), U4.6 (VDD)
GND: C4.1, C5.1, C6.1, C7.1, D2.2 (C), J1.6, J1.7, J2.6, J2.7, R12.2, U1.11 (V-), U4.2 (GND), U4.3 (GND), U4.5 (GND)
unnamed: C2.2, R6.1, R8.2, R14.2
unnamed: C3.1, R13.1
unnamed: C3.2, R1.1, R3.1, R7.2
unnamed: D1.1 (A), R2.2, R4.1
unnamed: D1.3 (COM), U1.8
unnamed: D1.2 (K), R1.2, R2.1, U1.9 (-)
unnamed: C2.1, D2.3 (K), R8.1, U1.13 (-)
unnamed: R11.2, R12.1, U1.3 (+)
unnamed: R9.2, R10.1, U1.2 (-)
unnamed: C1.1, R3.2, R4.2, R5.1, U1.6 (-)
detect: J1.5, J2.5, R10.2, U1.1
light-tight: J1.3, J2.3, R6.2, R13.2, U1.14
rect: C1.2, J1.4, J2.4, R5.2, R11.1, U1.7

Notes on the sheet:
PART VALUES NEED ADJUSTMENT
op-amp power
for less hectic PCB layout, the 4 stages of this op-amp could be rearranged
full-wave precision rectrifier generates DC signal from an AC input
AC coupling filter could be fancier filter if needed
voltage ref
check for light tight box by checking DC level at the detector output here
the detector stage op-amps use +3.3V and GND, and a +1.8V ref
difference amp subtracts the +1.8V reference to provide signal relative to GND suitable for A2D

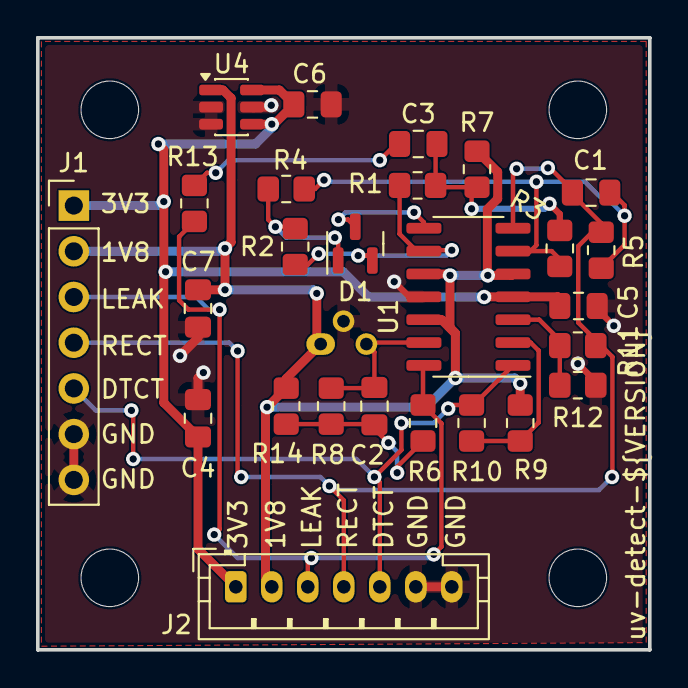
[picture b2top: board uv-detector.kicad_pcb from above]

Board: 2 copper layers, 34.0 x 34.0 mm, 31 parts (1 on the bottom side), 16 nets.

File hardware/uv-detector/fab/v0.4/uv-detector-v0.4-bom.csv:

"Refs","Value","Footprint","Qty","DNP","Description"
"C1,C3,CX4,CX5","1uF","Capacitor_SMD:C_0805_2012Metric_Pad1.18x1.45mm_HandSolder","4","",""
"C2","10pF","Capacitor_SMD:C_0805_2012Metric_Pad1.18x1.45mm_HandSolder","1","",""
"C4,C5","0.1uF","Capacitor_SMD:C_0805_2012Metric_Pad1.18x1.45mm_HandSolder","2","",""
"D1","BAT54S","Package_TO_SOT_SMD:SOT-23","1","",""
"D2","SD008-2171-112","Package_TO_SOT_THT:TO-18-3","1","","Si PIN Photodiode, 0.1 GHz, TO-18-3"
"H1,H2,H3,H4","MountingHole","MountingHole:MountingHole_3.2mm_M3","4","","Mounting Hole without connection"
"J1","Conn_01x06_Male","Connector_PinHeader_2.54mm:PinHeader_1x06_P2.54mm_Vertical","1","","Generic connector, single row, 01x06, script generated (kicad-library-utils/schlib/autogen/connector/)"
"J2","Conn_01x06_Male","Connector_JST:JST_PH_B6B-PH-K_1x06_P2.00mm_Vertical","1","","Generic connector, single row, 01x06, script generated (kicad-library-utils/schlib/autogen/connector/)"
"R1,R2,R3,R5,R7,R9,R11","10K","Resistor_SMD:R_0805_2012Metric_Pad1.20x1.40mm_HandSolder","7","",""
"R4,R15","4.99K","Resistor_SMD:R_0805_2012Metric_Pad1.20x1.40mm_HandSolder","2","",""
"R8","1Meg","Resistor_SMD:R_0805_2012Metric_Pad1.20x1.40mm_HandSolder","1","",""
"R14,RX13","1K","Resistor_SMD:R_0805_2012Metric_Pad1.20x1.40mm_HandSolder","2","",""
"RX6","100K","Resistor_SMD:R_0805_2012Metric_Pad1.20x1.40mm_HandSolder","1","",""
"RX10,RX12","43.2K","Resistor_SMD:R_0805_2012Metric_Pad1.20x1.40mm_HandSolder","2","",""
"U1","OPA4340UA","Package_SO:SOIC-14_3.9x8.7mm_P1.27mm","1","",""
"U2","LM4040DBZ-2.5","Package_TO_SOT_SMD:SOT-23","1","","2.500V Precision Micropower Shunt Voltage Reference, SOT-23"
